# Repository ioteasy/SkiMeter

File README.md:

# SkiMeter
Digital inclinometer and temperature sensor on ski pole
Measure current slope angle for assessing avalanche danger

# Future
- Barometric altitude

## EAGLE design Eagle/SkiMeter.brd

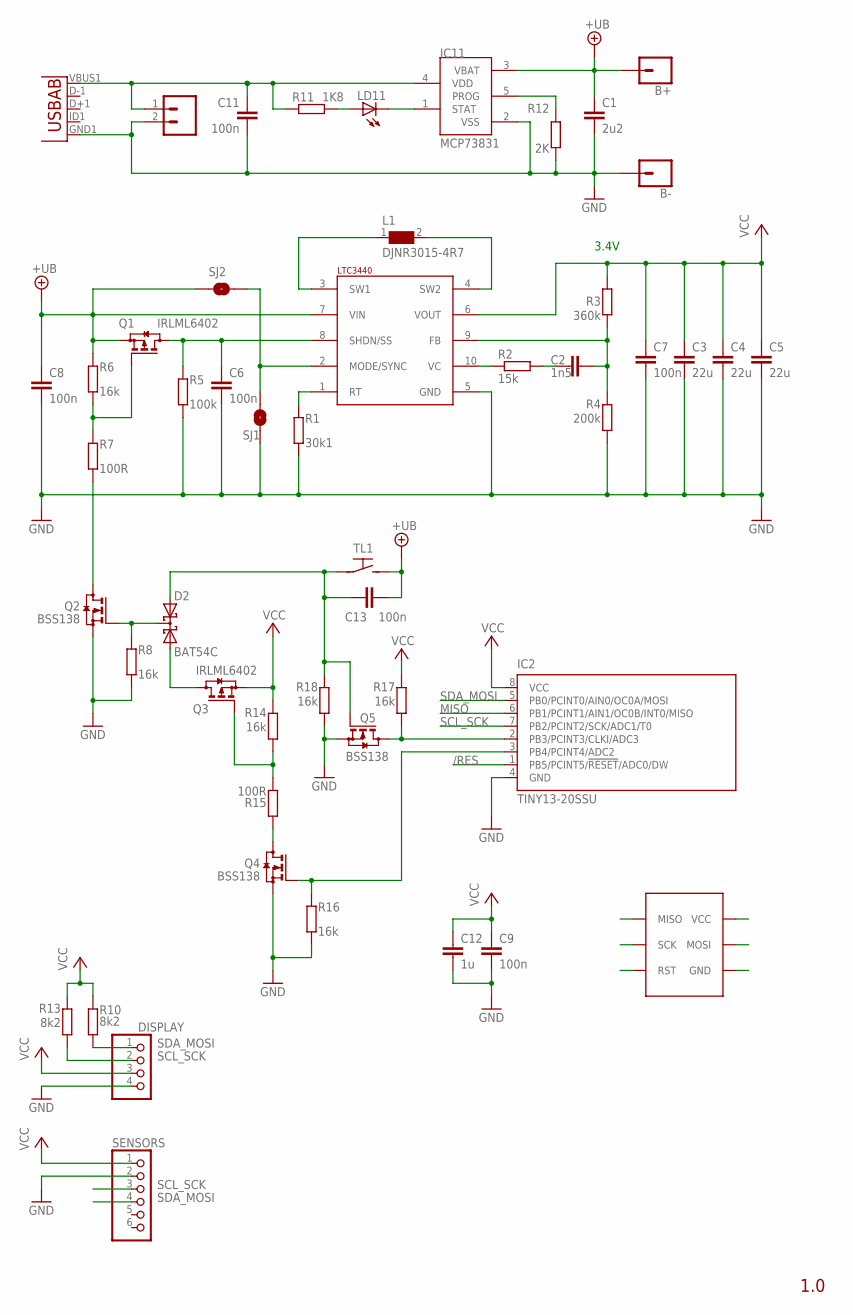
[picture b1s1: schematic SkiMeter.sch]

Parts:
+: CONN_02; 1X02
B+: CONN_01; 1X01
B-: CONN_01; 1X01
C1: 2u2; C0805
C2: 1n5; C0805
C3, C4, C5: 22u; C0805
C6, C7, C8, C9, C11, C13: 100n; C0805
C12: 1u; C0805
D2: BAT54C; SOT23
DISPLAY: PINHD-1X4; 1X04
IC1: LTC3440; MSOP10
IC2: TINY13-20SSU; 8S1
IC11: MCP73831; SOT23-5L
L1: DJNR3015-4R7; WE-LQS_3015
LD11: LEDCHIPLED_0805; CHIPLED_0805
Q1, Q3: IRLML6402; SOT23
Q2, Q4, Q5: BSS138; SOT23
R1: 30k1; M0805
R2: 15k; M0805
R3: 360k; M0805
R4: 200k; M0805
R5: 100k; M0805
R6, R8, R14, R16, R17, R18: 16k; M0805
R7, R15: 100R; M0805
R10, R13: 8k2; M0805
R11: 1K8; M0805
R12: 2K; M0805
SENSORS: PINHD-1X6; 1X06
SJ1: SOLDERJUMPERNO; SJ_2S-NO
SJ2: SOLDERJUMPERTRACE; SJ_2S-TRACE
TL1: TS1107GS
U1: USB""; USB-MICRO-SMD
U$1: ISP; ISP_PCB

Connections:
+UB: B+.1, C1.1, C8.1, C13.1, IC1.7 (VIN), IC11.3 (VBAT), Q1.2 (S), R6.1, SJ2.2, TL1.P$2 (S)
/RES: IC2.1 (PB5/PCINT5/!RESET!/ADC0/DW), U$1.P$5 (RST)
FB: C2.2, IC1.9 (FB), R3.1, R4.2
GND: +.2, B-.1, C1.2, C3.2, C4.2, C5.2, C6.2, C7.2, C8.2, C9.2, C11.1, C12.2, DISPLAY.4, IC1.5 (GND), IC2.4 (GND), IC11.2 (VSS), Q2.2 (S), Q4.2 (S), Q5.2 (S), R1.2, R4.1, R5.2, R8.2, R12.1, R16.2, R18.2, SENSORS.2, SJ1.1, U1.GND1 (GND), U$1.P$6 (GND)
MISO: IC2.6 (PB1/PCINT1/AIN1/OC0B/INT0/MISO), U$1.P$1 (MISO)
unnamed: IC1.1 (RT), R1.1
unnamed: C6.1, IC1.8 (SHDN/SS), Q1.3 (D), R5.1
unnamed: C2.1, R2.2
unnamed: Q1.1 (G), R6.2, R7.1
unnamed: Q2.3 (D), R7.2
unnamed: IC1.10 (VC), R2.1
unnamed: D2.3 (CC), Q2.1 (G), R8.1
unnamed: D2.1 (A1), Q3.3 (D)
unnamed: IC11.5 (PROG), R12.2
unnamed: IC11.1 (STAT), LD11.C
unnamed: LD11.A, R11.1
unnamed: C13.2, D2.2 (A2), Q5.1 (G), R18.1, TL1.P$1
unnamed: Q3.1 (G), R14.2, R15.1
unnamed: Q4.3 (D), R15.2
unnamed: IC2.3 (PB4/PCINT4/ADC2), Q4.1 (G), R16.1
unnamed: IC2.2 (PB3/PCINT3/CLKI/ADC3), Q5.3 (D), R17.2
unnamed: IC1.2 (MODE/SYNC), SJ1.2, SJ2.1
SCL_SCK: DISPLAY.2, IC2.7 (PB2/PCINT2/SCK/ADC1/T0), R13.2, SENSORS.3, U$1.P$3 (SCK)
SDA_MOSI: DISPLAY.1, IC2.5 (PB0/PCINT0/AIN0/OC0A/MOSI), R10.2, SENSORS.4, U$1.P$4 (MOSI)
SW1: IC1.3 (SW1), L1.1
SW2: IC1.4 (SW2), L1.2
U_CHARG: +.1, C11.2, IC11.4 (VDD), R11.2, U1.VBUS1 (VBUS)
VCC: C3.1, C4.1, C5.1, C7.1, C9.1, C12.1, DISPLAY.3, IC1.6 (VOUT), IC2.8 (VCC), Q3.2 (S), R3.2, R10.1, R13.1, R14.1, R17.1, SENSORS.1, U$1.P$2 (VCC)

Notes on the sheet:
3.4V

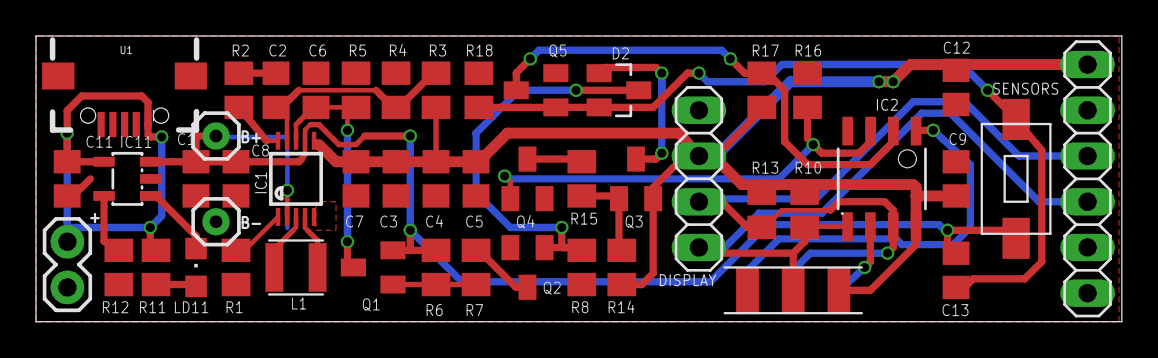
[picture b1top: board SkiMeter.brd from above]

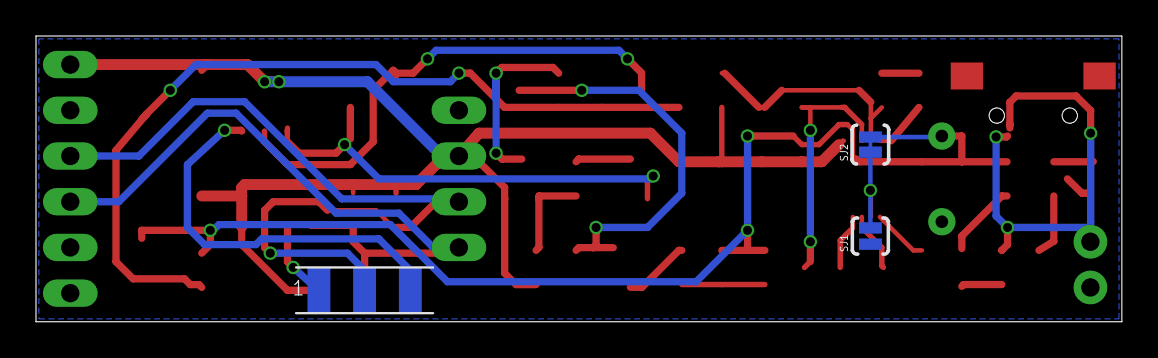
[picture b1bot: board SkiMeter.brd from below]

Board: 2 copper layers, 60.3 x 15.9 mm, 50 parts (3 on the bottom side), 28 nets.

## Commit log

2018-05-03 add files
2018-05-21 readme
2018-05-22 add pcb
2018-05-22 add Box model

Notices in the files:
parts and their libraries:
Wurth_Elektronik_Passive_rev15b: Copyright: Würth Elektronik
SparkFun-Connectors: Licensing: Creative Commons ShareAlike 4.0 International - https://creativecommons.org/licenses/by-sa/4.0
